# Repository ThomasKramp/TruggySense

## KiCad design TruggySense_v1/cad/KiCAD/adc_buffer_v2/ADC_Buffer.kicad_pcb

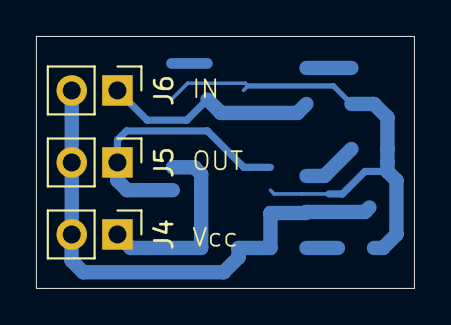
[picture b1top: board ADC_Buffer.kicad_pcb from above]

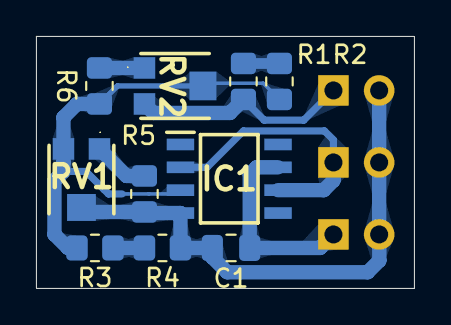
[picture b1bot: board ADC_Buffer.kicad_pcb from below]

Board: 2 copper layers, 21.0 x 14.0 mm, 13 parts (10 on the bottom side), 9 nets.

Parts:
C1: 10µ; C_0805_2012Metric_Pad1.18x1.45mm_HandSolder
IC1: OPA350UA_2K5; SOIC127P600X175-8N
J4, J5, J6: Conn_01x02; PinHeader_1x02_P2.54mm_Vertical
R1, R2, R3, R4, R5, R6: R; R_0805_2012Metric_Pad1.20x1.40mm_HandSolder
RV1, RV2: R; TC33X2503E

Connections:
GND: C1.2, IC1.4 (V-), J4.2, J5.2, J6.2, R4.1, R5.2, RV1.2
unnamed: IC1.3 (+IN), R2.2, R3.2, R6.2, RV1.3, RV2.2
unnamed: IC1.2 (-IN), IC1.6 (OUTPUT), J5.1
unnamed: J6.1, R1.1, RV2.3
unnamed: R1.2, R2.1
unnamed: R3.1, R4.2
unnamed: R5.1, RV1.1
unnamed: R6.1, RV2.1
VCC: C1.1, IC1.7 (V+), J4.1

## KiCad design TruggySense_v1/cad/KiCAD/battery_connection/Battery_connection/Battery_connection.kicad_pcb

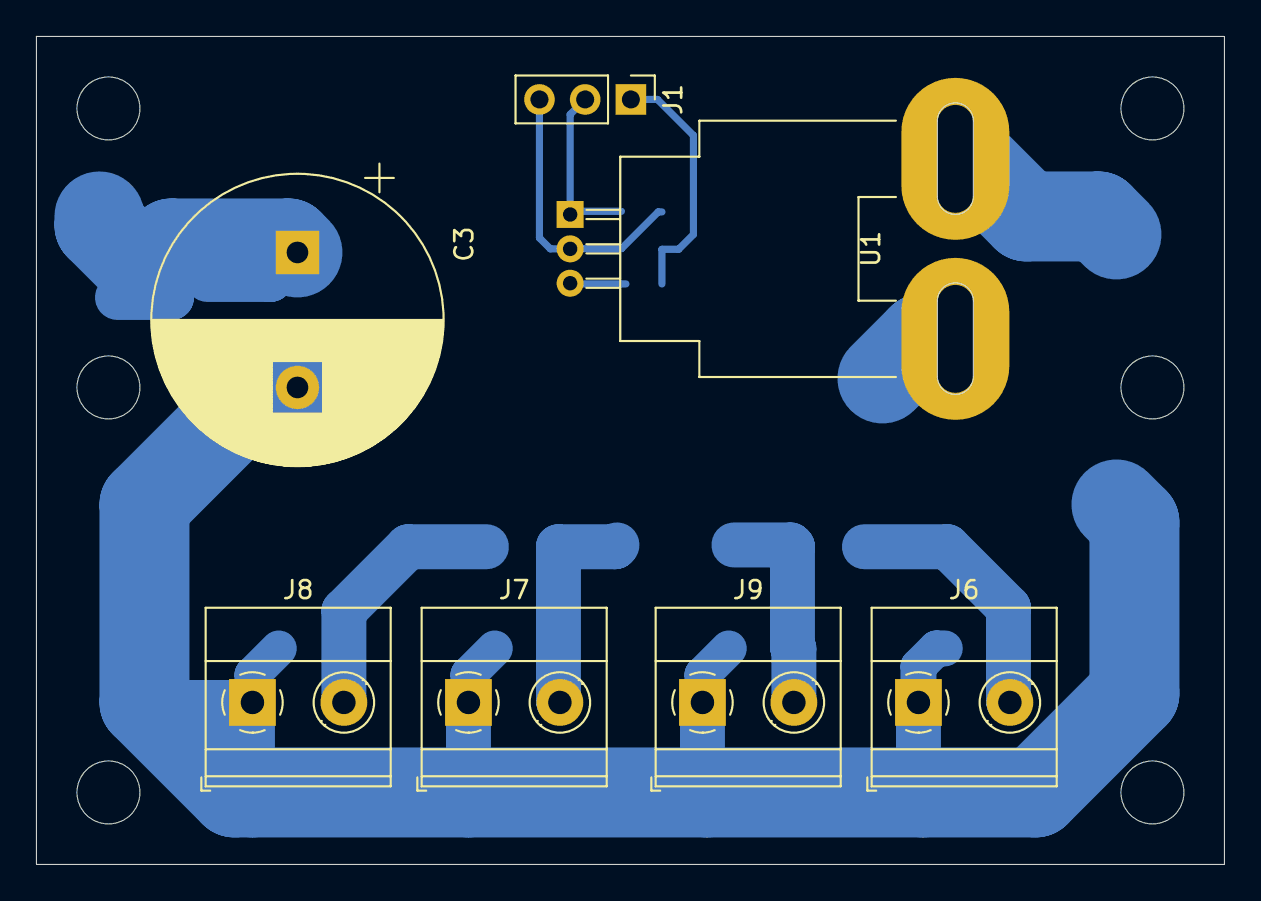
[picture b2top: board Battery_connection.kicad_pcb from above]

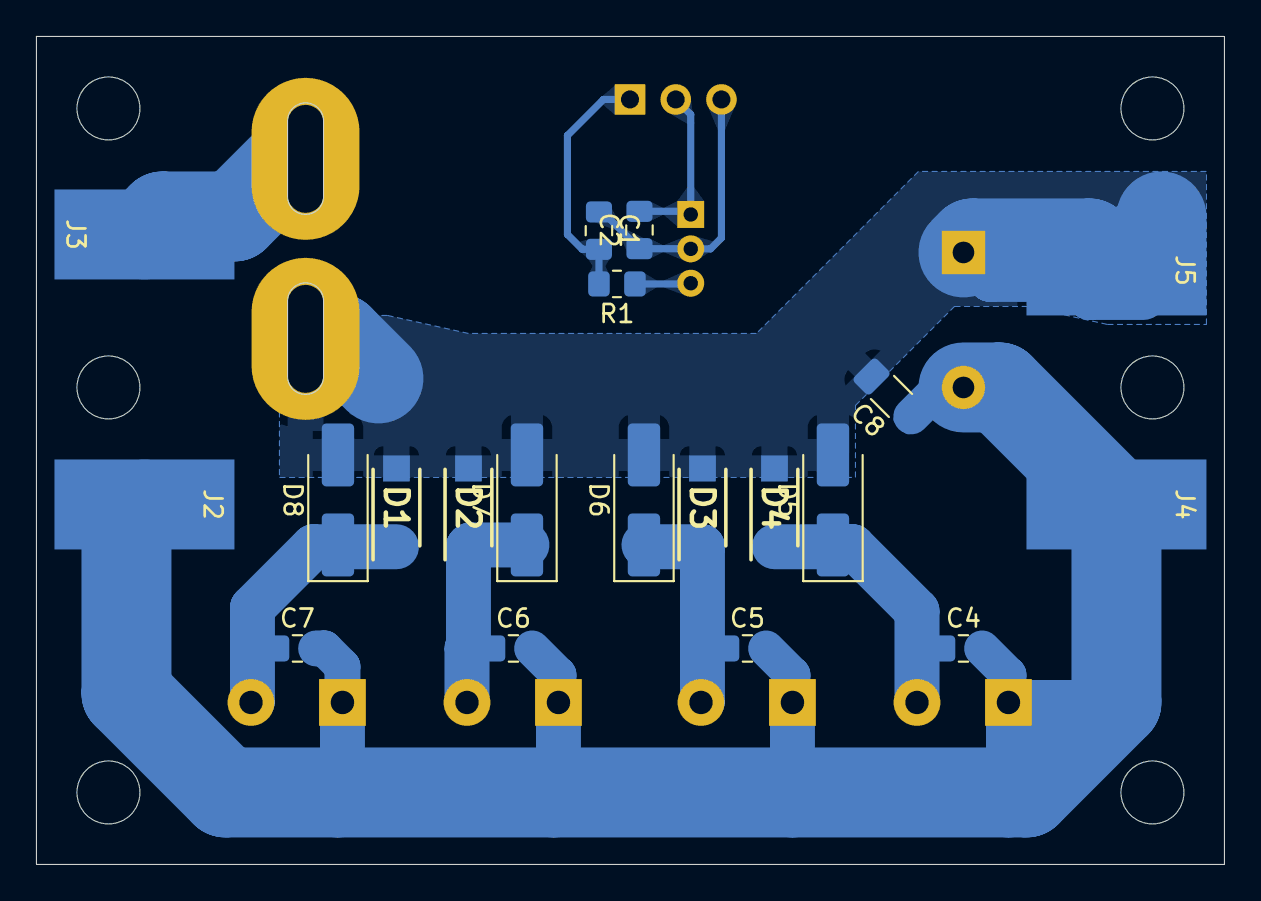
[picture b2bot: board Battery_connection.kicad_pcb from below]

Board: 2 copper layers, 66.0 x 46.0 mm, 27 parts (20 on the bottom side), 11 nets.

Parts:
C1: 1µ; C_0805_2012Metric_Pad1.18x1.45mm_HandSolder
C2: 100n; C_0805_2012Metric_Pad1.18x1.45mm_HandSolder
C3: 1000µ; CP_Radial_D16.0mm_P7.50mm
C4, C5, C6, C7: 10µ; C_0805_2012Metric_Pad1.18x1.45mm_HandSolder
C8: 10µ; C_1206_3216Metric_Pad1.33x1.80mm_HandSolder
D1, D2, D3, D4: VSSAF5M10HM3; SODFL5226X100N
D5, D6, D7, D8: 1N4007; D_SMA_Handsoldering
J1: Supply_I_Sens; PinHeader_1x03_P2.54mm_Vertical
J2: ESC-; SolderWirePad_1x01_SMD_5x10mm
J3: ESC+; SolderWirePad_1x01_SMD_5x10mm
J4: BAT-; SolderWirePad_1x01_SMD_5x10mm
J5: BAT+; SolderWirePad_1x01_SMD_5x10mm
J6: JET_5V; TerminalBlock_Phoenix_MKDS-1,5-2-5.08_1x02_P5.08mm_Horizont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
J7: TEENSY_3V3; TerminalBlock_Phoenix_MKDS-1,5-2-5.08_1x02_P5.08mm_Horizont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
J8: PHERI_3V3; TerminalBlock_Phoenix_MKDS-1,5-2-5.08_1x02_P5.08mm_Horizont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
J9: PHERI_5V; TerminalBlock_Phoenix_MKDS-1,5-2-5.08_1x02_P5.08mm_Horizont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
R1: 8k2; R_0805_2012Metric_Pad1.20x1.40mm_HandSolder
U1: ACS758xCB-200B-PFF; Allegro_CB_PFF

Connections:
+3.3V: C2.2, J1.2, U1.1 (VCC)
GND: C3.2, C4.2, C5.2, C6.2, C7.2, C8.1, J2.1, J4.1, J6.1, J7.1, J8.1, J9.1
GND2: C1.1, C2.1, J1.3, U1.2 (GND)
unnamed: C7.1, D1.1 (K), D8.1 (K), J6.2
unnamed: C6.1, D2.1 (K), D7.1 (K), J9.2
unnamed: C5.1, D3.1 (K), D6.1 (K), J7.2
unnamed: C4.1, D4.1 (K), D5.1 (K), J8.2
unnamed: C1.2, J1.1, R1.2
unnamed: J3.1, U1.5 (IP-)
unnamed: R1.1, U1.3 (VIOUT)
VCC: C3.1, C8.2, D1.2 (A), D2.2 (A), D3.2 (A), D4.2 (A), D5.2 (A), D6.2 (A), D7.2 (A), D8.2 (A), J5.1, U1.4 (IP+)

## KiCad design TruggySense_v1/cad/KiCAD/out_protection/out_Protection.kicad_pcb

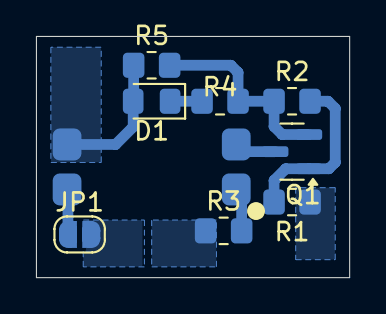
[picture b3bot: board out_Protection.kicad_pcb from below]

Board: 2 copper layers, 17.4 x 13.4 mm, 9 parts (9 on the bottom side), 7 nets.

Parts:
D1: LED; LED_0805_2012Metric_Pad1.15x1.40mm_HandSolder
JP1: SolderJumper_2_Open; SolderJumper-2_P1.3mm_Open_RoundedPad1.0x1.5mm
Q1: AO3400A; SOT-23
R1: 100; R_0805_2012Metric_Pad1.20x1.40mm_HandSolder
R2: 10k; R_0805_2012Metric_Pad1.20x1.40mm_HandSolder
R3: 39; R_0805_2012Metric_Pad1.20x1.40mm_HandSolder
R4: 330; R_0805_2012Metric_Pad1.20x1.40mm_HandSolder
R5: 1k; R_0805_2012Metric_Pad1.20x1.40mm_HandSolder
U1: VOS618A; VO617A

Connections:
/OUT_1: D1.2 (A), R5.1, U1.3
GND: Q1.2 (S), R2.1, R4.2, R5.2
unnamed: D1.1 (K), R4.1
unnamed: JP1.1 (A), U1.4
unnamed: Q1.3 (D), U1.2
unnamed: Q1.1 (G), R1.2, R2.2
unnamed: R3.2, U1.1

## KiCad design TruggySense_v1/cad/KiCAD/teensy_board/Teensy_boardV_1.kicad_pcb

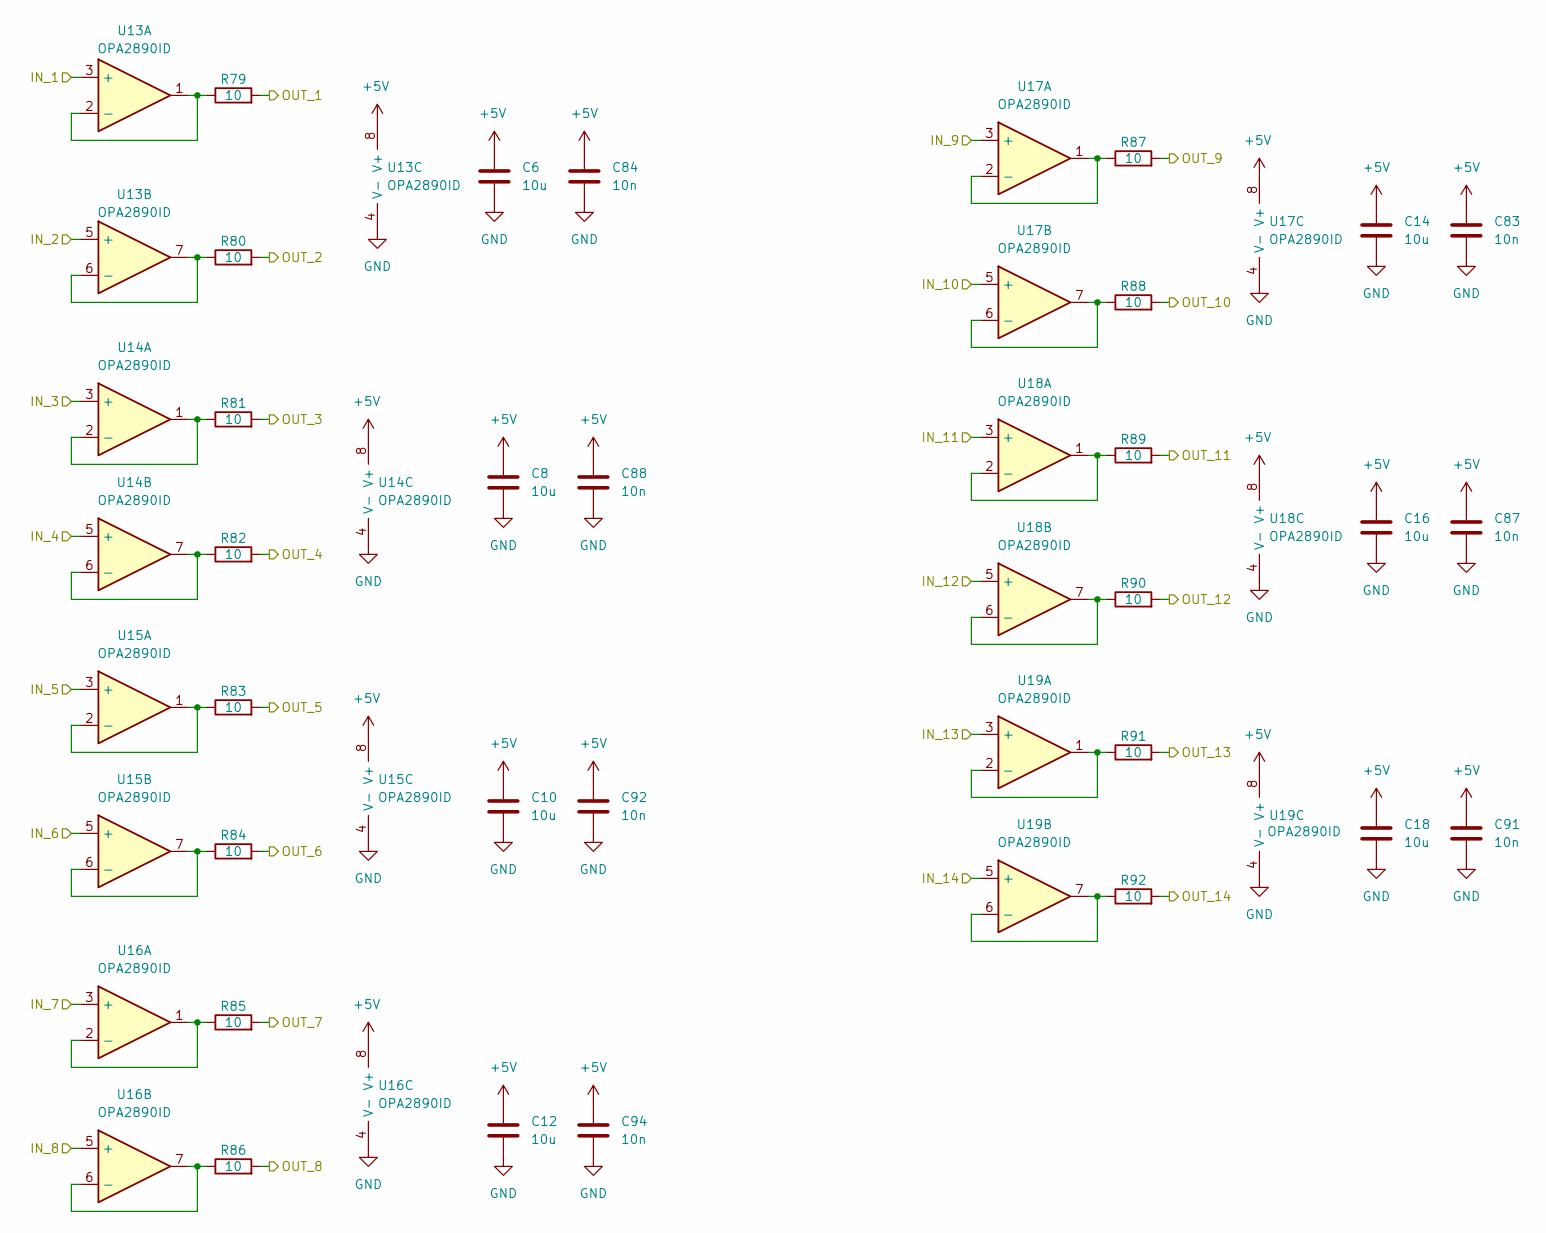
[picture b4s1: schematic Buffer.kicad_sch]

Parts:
C6, C8, C10, C12, C14, C16, C18: 10u; C_0805_2012Metric_Pad1.18x1.45mm_HandSolder
C83, C84, C87, C88, C91, C92, C94: 10n; C_0805_2012Metric_Pad1.18x1.45mm_HandSolder
R79, R80, R81, R82, R83, R84, R85, R86, R87, R88, R89, R90, R91, R92: 10; C_0805_2012Metric_Pad1.18x1.45mm_HandSolder
U13: OPA2890ID; SOIC-8_3.9x4.9mm_P1.27mm
U14, U15, U16, U17, U18, U19: OPA2890ID; SO-8_3.9x4.9mm_P1.27mm

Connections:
+5V: C6.1, C8.1, C10.1, C12.1, C14.1, C16.1, C18.1, C83.1, C84.1, C87.1, C88.1, C91.1, C92.1, C94.1, U13.8 (V+), U14.8 (V+), U15.8 (V+), U16.8 (V+), U17.8 (V+), U18.8 (V+), U19.8 (V+); also elsewhere on the board
/ADC inputs/Buffer/IN_1: U13.3 (+); also elsewhere on the board
/ADC inputs/Buffer/IN_2: U13.5 (+); also elsewhere on the board
/ADC inputs/Buffer/IN_3: U14.3 (+); also elsewhere on the board
/ADC inputs/Buffer/IN_4: U14.5 (+); also elsewhere on the board
/ADC inputs/Buffer/IN_5: U15.3 (+); also elsewhere on the board
/ADC inputs/Buffer/IN_6: U15.5 (+); also elsewhere on the board
/ADC inputs/Buffer/IN_7: U16.3 (+); also elsewhere on the board
/ADC inputs/Buffer/IN_8: U16.5 (+); also elsewhere on the board
/ADC inputs/Buffer/IN_9: U17.3 (+); also elsewhere on the board
/ADC inputs/Buffer/IN_10: U17.5 (+); also elsewhere on the board
/ADC inputs/Buffer/IN_11: U18.3 (+); also elsewhere on the board
/ADC inputs/Buffer/IN_12: U18.5 (+); also elsewhere on the board
/ADC inputs/Buffer/IN_13: U19.3 (+); also elsewhere on the board
/ADC inputs/Buffer/IN_14: U19.5 (+); also elsewhere on the board
/ADC inputs/Buffer/OUT_1: R79.2; also elsewhere on the board
/ADC inputs/Buffer/OUT_2: R80.2; also elsewhere on the board
/ADC inputs/Buffer/OUT_3: R81.2; also elsewhere on the board
/ADC inputs/Buffer/OUT_4: R82.2; also elsewhere on the board
/ADC inputs/Buffer/OUT_5: R83.2; also elsewhere on the board
/ADC inputs/Buffer/OUT_6: R84.2; also elsewhere on the board
/ADC inputs/Buffer/OUT_7: R85.2; also elsewhere on the board
/ADC inputs/Buffer/OUT_8: R86.2; also elsewhere on the board
/ADC inputs/Buffer/OUT_9: R87.2; also elsewhere on the board
/ADC inputs/Buffer/OUT_10: R88.2; also elsewhere on the board
/ADC inputs/Buffer/OUT_11: R89.2; also elsewhere on the board
/ADC inputs/Buffer/OUT_12: R90.2; also elsewhere on the board
/ADC inputs/Buffer/OUT_13: R91.2; also elsewhere on the board
/ADC inputs/Buffer/OUT_14: R92.2; also elsewhere on the board
GND: C6.2, C8.2, C10.2, C12.2, C14.2, C16.2, C18.2, C83.2, C84.2, C87.2, C88.2, C91.2, C92.2, C94.2, U13.4 (V-), U14.4 (V-), U15.4 (V-), U16.4 (V-), U17.4 (V-), U18.4 (V-), U19.4 (V-); also elsewhere on the board
unnamed: R79.1, U13.1, U13.2 (-)
unnamed: R80.1, U13.6 (-), U13.7
unnamed: R81.1, U14.1, U14.2 (-)
unnamed: R82.1, U14.6 (-), U14.7
unnamed: R83.1, U15.1, U15.2 (-)
unnamed: R84.1, U15.6 (-), U15.7
unnamed: R85.1, U16.1, U16.2 (-)
unnamed: R86.1, U16.6 (-), U16.7
unnamed: R87.1, U17.1, U17.2 (-)
unnamed: R88.1, U17.6 (-), U17.7
unnamed: R89.1, U18.1, U18.2 (-)
unnamed: R90.1, U18.6 (-), U18.7
unnamed: R91.1, U19.1, U19.2 (-)
unnamed: R92.1, U19.6 (-), U19.7

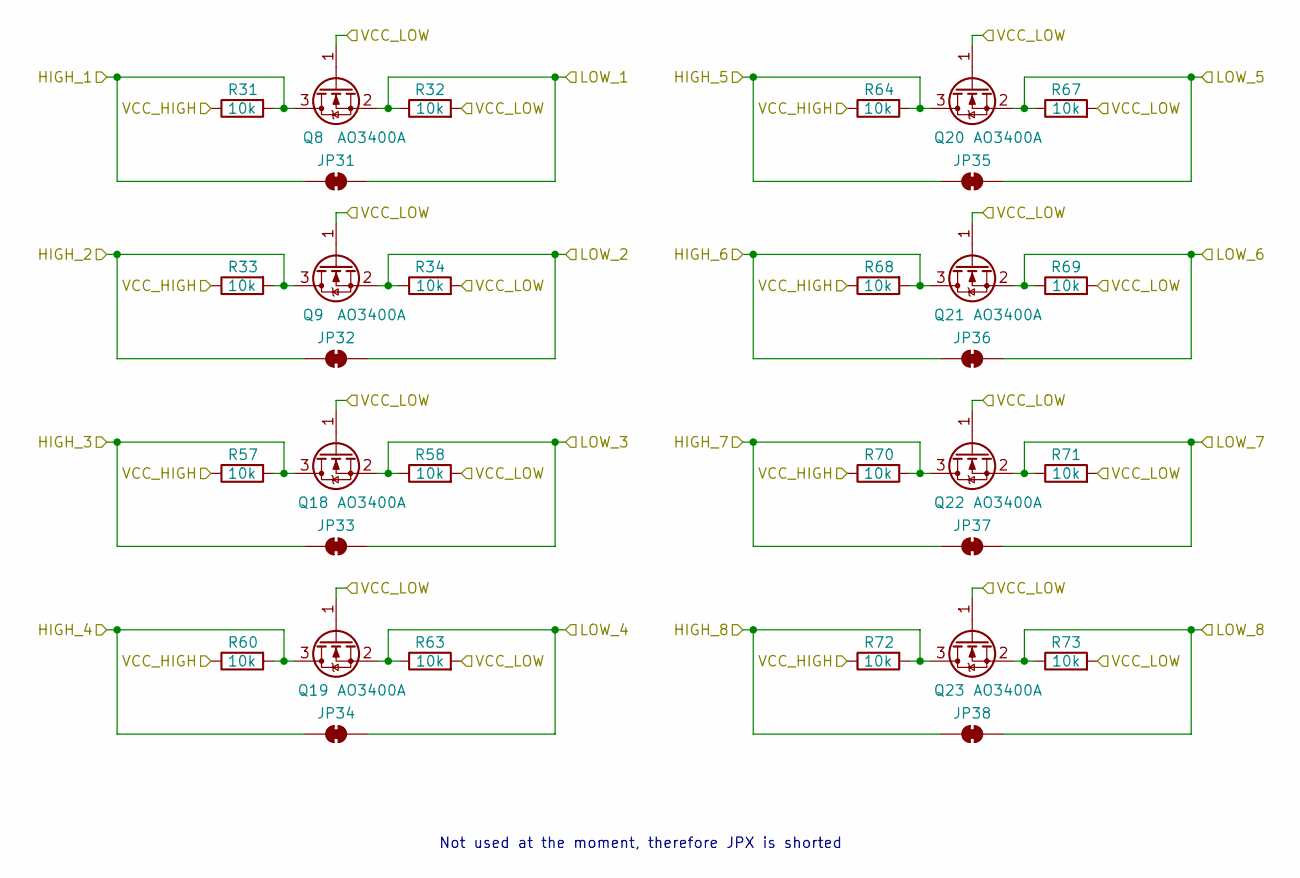
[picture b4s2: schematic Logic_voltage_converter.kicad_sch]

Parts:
JP31, JP32, JP33, JP34, JP35, JP36, JP37, JP38: SolderJumper_2_Bridged; SolderJumper-2_P1.3mm_Bridged_RoundedPad1.0x1.5mm
Q8, Q9, Q18, Q19, Q20, Q21, Q22, Q23: AO3400A; SOT-23
R31, R32, R33, R34, R57, R58, R60, R63, R64, R67, R68, R69, R70, R71, R72, R73: 10k; R_0805_2012Metric_Pad1.20x1.40mm_HandSolder

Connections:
+5V: R31.1, R33.1, R57.1, R60.1, R64.1, R68.1, R70.1, R72.1; also elsewhere on the board
/Communication & pheripherals/Logic_voltage_converter/HIGH_1: JP31.1 (A), Q8.3 (D), R31.2; also elsewhere on the board
/Communication & pheripherals/Logic_voltage_converter/HIGH_2: JP32.1 (A), Q9.3 (D), R33.2; also elsewhere on the board
/Communication & pheripherals/Logic_voltage_converter/HIGH_3: JP33.1 (A), Q18.3 (D), R57.2; also elsewhere on the board
/Communication & pheripherals/Logic_voltage_converter/HIGH_4: JP34.1 (A), Q19.3 (D), R60.2; also elsewhere on the board
/Communication & pheripherals/Logic_voltage_converter/HIGH_5: JP35.1 (A), Q20.3 (D), R64.2; also elsewhere on the board
/Communication & pheripherals/Logic_voltage_converter/HIGH_6: JP36.1 (A), Q21.3 (D), R68.2; also elsewhere on the board
/Communication & pheripherals/Logic_voltage_converter/HIGH_7: JP37.1 (A), Q22.3 (D), R70.2; also elsewhere on the board
/Communication & pheripherals/Logic_voltage_converter/HIGH_8: JP38.1 (A), Q23.3 (D), R72.2; also elsewhere on the board
/Communication & pheripherals/Logic_voltage_converter/LOW_1: JP31.2 (B), Q8.2 (S), R32.1; also elsewhere on the board
/Communication & pheripherals/Logic_voltage_converter/LOW_2: JP32.2 (B), Q9.2 (S), R34.1; also elsewhere on the board
/Communication & pheripherals/Logic_voltage_converter/LOW_3: JP33.2 (B), Q18.2 (S), R58.1; also elsewhere on the board
/Communication & pheripherals/Logic_voltage_converter/LOW_4: JP34.2 (B), Q19.2 (S), R63.1; also elsewhere on the board
/Communication & pheripherals/Logic_voltage_converter/LOW_5: JP35.2 (B), Q20.2 (S), R67.1; also elsewhere on the board
/Communication & pheripherals/Logic_voltage_converter/LOW_6: JP36.2 (B), Q21.2 (S), R69.1; also elsewhere on the board
/Communication & pheripherals/Logic_voltage_converter/LOW_7: JP37.2 (B), Q22.2 (S), R71.1; also elsewhere on the board
/Communication & pheripherals/Logic_voltage_converter/LOW_8: JP38.2 (B), Q23.2 (S), R73.1; also elsewhere on the board

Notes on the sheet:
Not used at the moment, therefore JPX is shorted

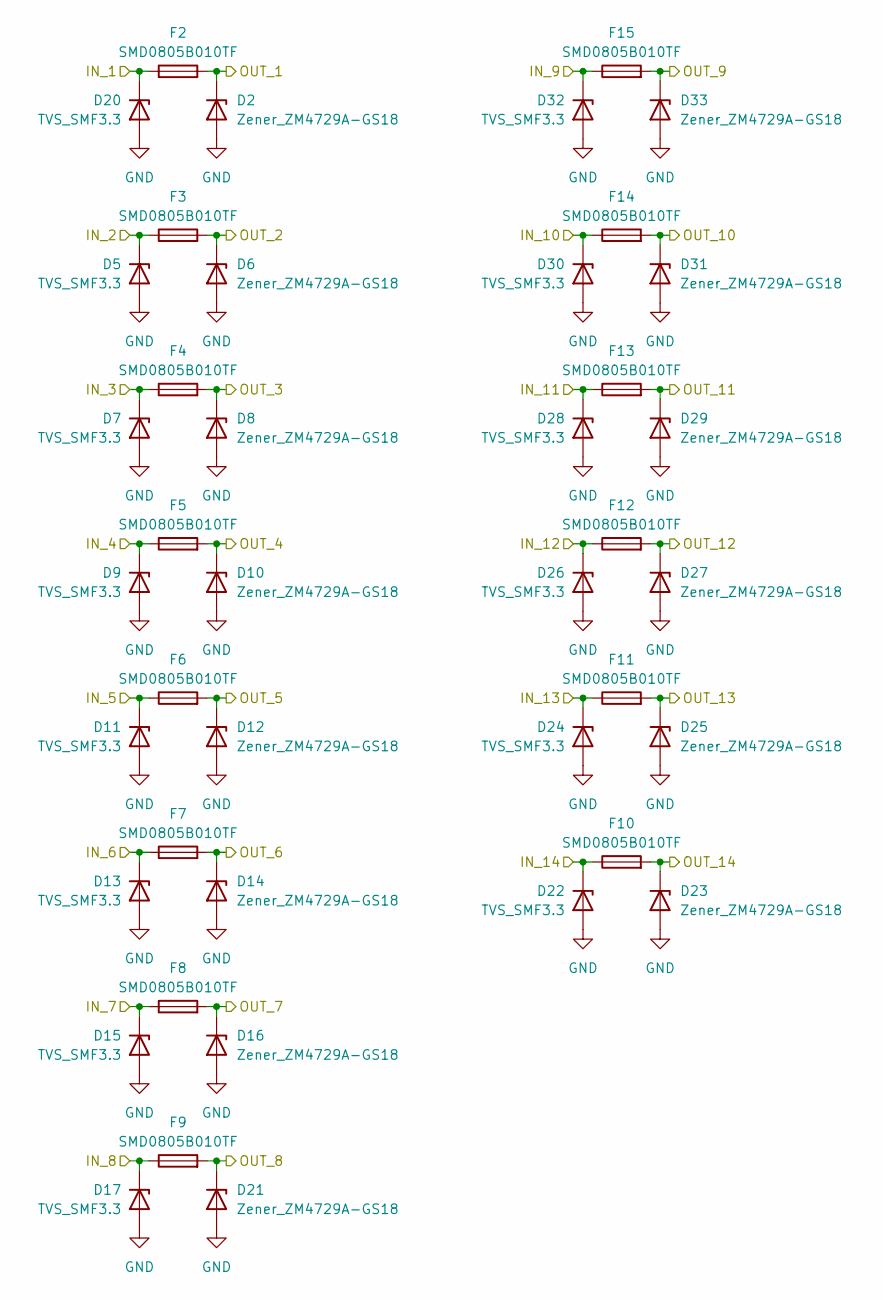
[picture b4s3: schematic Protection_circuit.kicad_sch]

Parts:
D2, D6, D8, D10, D12, D14, D16, D21, D23, D25, D27, D29, D31, D33: Zener_ZM4729A-GS18; D_MELF
D5, D7, D9, D11, D13, D15, D17, D20, D22, D24, D26, D28, D30, D32: TVS_SMF3.3; SOD3718X108N
F2, F3, F4, F5, F6, F7, F8, F9, F10, F11, F12, F13, F14, F15: SMD0805B010TF; Fuse_0805_2012Metric_Pad1.15x1.40mm_HandSolder

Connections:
/ADC inputs/Protection_circuit_ADC1/IN_1: D20.1 (K), F2.1; also elsewhere on the board
/ADC inputs/Protection_circuit_ADC1/IN_2: D5.1 (K), F3.1; also elsewhere on the board
/ADC inputs/Protection_circuit_ADC1/IN_3: D7.1 (K), F4.1; also elsewhere on the board
/ADC inputs/Protection_circuit_ADC1/IN_4: D9.1 (K), F5.1; also elsewhere on the board
/ADC inputs/Protection_circuit_ADC1/IN_5: D11.1 (K), F6.1; also elsewhere on the board
/ADC inputs/Protection_circuit_ADC1/IN_6: D13.1 (K), F7.1; also elsewhere on the board
/ADC inputs/Protection_circuit_ADC1/IN_7: D15.1 (K), F8.1; also elsewhere on the board
/ADC inputs/Protection_circuit_ADC1/IN_8: D17.1 (K), F9.1; also elsewhere on the board
/ADC inputs/Protection_circuit_ADC1/IN_9: D32.1 (K), F15.1; also elsewhere on the board
/ADC inputs/Protection_circuit_ADC1/IN_10: D30.1 (K), F14.1; also elsewhere on the board
/ADC inputs/Protection_circuit_ADC1/IN_11: D28.1 (K), F13.1; also elsewhere on the board
/ADC inputs/Protection_circuit_ADC1/IN_12: D26.1 (K), F12.1; also elsewhere on the board
/ADC inputs/Protection_circuit_ADC1/IN_13: D24.1 (K), F11.1; also elsewhere on the board
/ADC inputs/Protection_circuit_ADC1/IN_14: D22.1 (K), F10.1; also elsewhere on the board
/ADC inputs/Protection_circuit_ADC1/OUT_1: D2.1 (K), F2.2; also elsewhere on the board
/ADC inputs/Protection_circuit_ADC1/OUT_2: D6.1 (K), F3.2; also elsewhere on the board
/ADC inputs/Protection_circuit_ADC1/OUT_3: D8.1 (K), F4.2; also elsewhere on the board
/ADC inputs/Protection_circuit_ADC1/OUT_4: D10.1 (K), F5.2; also elsewhere on the board
/ADC inputs/Protection_circuit_ADC1/OUT_5: D12.1 (K), F6.2; also elsewhere on the board
/ADC inputs/Protection_circuit_ADC1/OUT_6: D14.1 (K), F7.2; also elsewhere on the board
/ADC inputs/Protection_circuit_ADC1/OUT_7: D16.1 (K), F8.2; also elsewhere on the board
/ADC inputs/Protection_circuit_ADC1/OUT_8: D21.1 (K), F9.2; also elsewhere on the board
/ADC inputs/Protection_circuit_ADC1/OUT_9: D33.1 (K), F15.2; also elsewhere on the board
/ADC inputs/Protection_circuit_ADC1/OUT_10: D31.1 (K), F14.2; also elsewhere on the board
/ADC inputs/Protection_circuit_ADC1/OUT_11: D29.1 (K), F13.2; also elsewhere on the board
/ADC inputs/Protection_circuit_ADC1/OUT_12: D27.1 (K), F12.2; also elsewhere on the board
/ADC inputs/Protection_circuit_ADC1/OUT_13: D25.1 (K), F11.2; also elsewhere on the board
/ADC inputs/Protection_circuit_ADC1/OUT_14: D23.1 (K), F10.2; also elsewhere on the board
GND: D2.2 (A), D5.2 (A), D6.2 (A), D7.2 (A), D8.2 (A), D9.2 (A), D10.2 (A), D11.2 (A), D12.2 (A), D13.2 (A), D14.2 (A), D15.2 (A), D16.2 (A), D17.2 (A), D20.2 (A), D21.2 (A), D22.2 (A), D23.2 (A), D24.2 (A), D25.2 (A), D26.2 (A), D27.2 (A), D28.2 (A), D29.2 (A), D30.2 (A), D31.2 (A), D32.2 (A), D33.2 (A); also elsewhere on the board

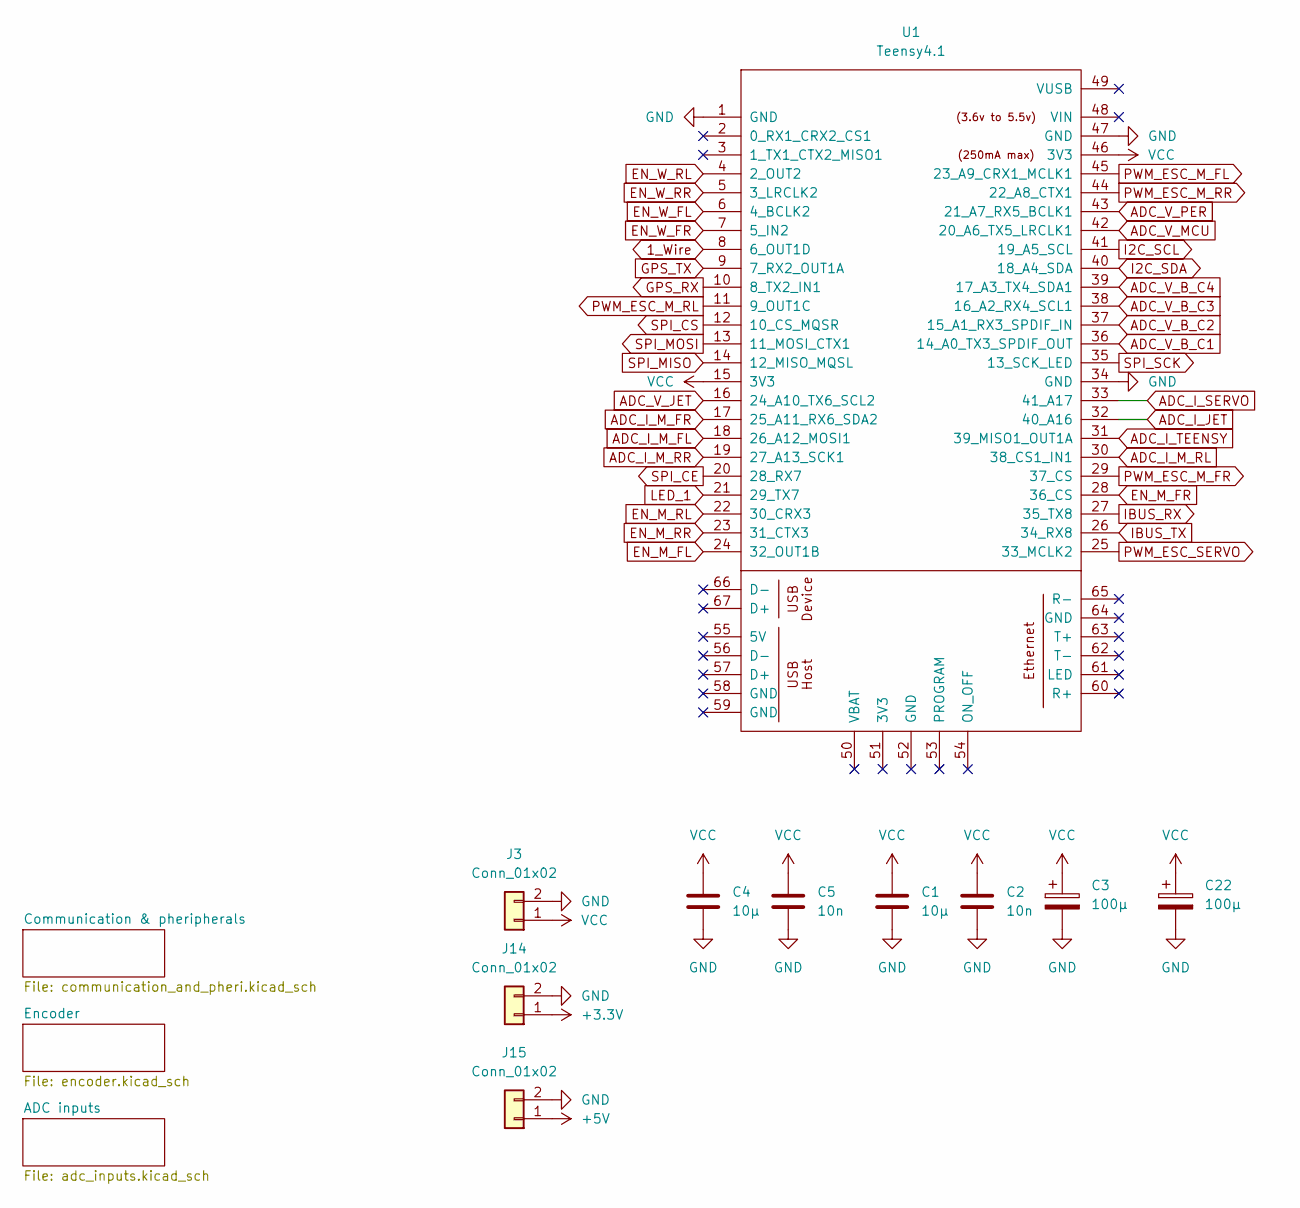
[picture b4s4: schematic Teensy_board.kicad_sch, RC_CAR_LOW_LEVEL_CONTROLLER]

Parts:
C1, C4: 10µ; C_0805_2012Metric_Pad1.18x1.45mm_HandSolder
C2, C5: 10n; C_0805_2012Metric_Pad1.18x1.45mm_HandSolder
C3, C22: 100µ; CP_Radial_D5.0mm_P2.00mm
J3, J14, J15: Conn_01x02; PinSocket_1x02_P2.54mm_Vertical
U1: Teensy4.1; Teensy41

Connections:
1_Wire: U1.8 (6_OUT1D); also elsewhere on the board
+5V: J15.1; also elsewhere on the board
ADC_I_JET: U1.32 (40_A16); also elsewhere on the board
ADC_I_M_FL: U1.18 (26_A12_MOSI1); also elsewhere on the board
ADC_I_M_FR: U1.17 (25_A11_RX6_SDA2); also elsewhere on the board
ADC_I_M_RL: U1.30 (38_CS1_IN1); also elsewhere on the board
ADC_I_M_RR: U1.19 (27_A13_SCK1); also elsewhere on the board
ADC_I_SERVO: U1.33 (41_A17); also elsewhere on the board
ADC_I_TEENSY: U1.31 (39_MISO1_OUT1A); also elsewhere on the board
ADC_V_B_C1: U1.36 (14_A0_TX3_SPDIF_OUT); also elsewhere on the board
ADC_V_B_C2: U1.37 (15_A1_RX3_SPDIF_IN); also elsewhere on the board
ADC_V_B_C3: U1.38 (16_A2_RX4_SCL1); also elsewhere on the board
ADC_V_B_C4: U1.39 (17_A3_TX4_SDA1); also elsewhere on the board
ADC_V_JET: U1.16 (24_A10_TX6_SCL2); also elsewhere on the board
ADC_V_MCU: U1.42 (20_A6_TX5_LRCLK1); also elsewhere on the board
ADC_V_PER: U1.43 (21_A7_RX5_BCLK1); also elsewhere on the board
EN_M_FL: U1.24 (32_OUT1B); also elsewhere on the board
EN_M_FR: U1.28 (36_CS); also elsewhere on the board
EN_M_RL: U1.22 (30_CRX3); also elsewhere on the board
EN_M_RR: U1.23 (31_CTX3); also elsewhere on the board
EN_W_FL: U1.6 (4_BCLK2); also elsewhere on the board
EN_W_FR: U1.7 (5_IN2); also elsewhere on the board
EN_W_RL: U1.4 (2_OUT2); also elsewhere on the board
EN_W_RR: U1.5 (3_LRCLK2); also elsewhere on the board
GND: C1.2, C2.2, C3.2, C4.2, C5.2, C22.2, J3.2, J14.2, J15.2, U1.1 (GND), U1.34 (GND), U1.47 (GND); also elsewhere on the board
GPS_RX: U1.10 (8_TX2_IN1); also elsewhere on the board
GPS_TX: U1.9 (7_RX2_OUT1A); also elsewhere on the board
I2C_SCL: U1.41 (19_A5_SCL); also elsewhere on the board
I2C_SDA: U1.40 (18_A4_SDA); also elsewhere on the board
IBUS_RX: U1.27 (35_TX8); also elsewhere on the board
IBUS_TX: U1.26 (34_RX8); also elsewhere on the board
PWM_ESC_M_FL: U1.45 (23_A9_CRX1_MCLK1); also elsewhere on the board
PWM_ESC_M_FR: U1.29 (37_CS); also elsewhere on the board
PWM_ESC_M_RL: U1.11 (9_OUT1C); also elsewhere on the board
PWM_ESC_M_RR: U1.44 (22_A8_CTX1); also elsewhere on the board
PWM_ESC_SERVO: U1.25 (33_MCLK2); also elsewhere on the board
SPI_CS: U1.12 (10_CS_MQSR); also elsewhere on the board
SPI_MISO: U1.14 (12_MISO_MQSL); also elsewhere on the board
SPI_MOSI: U1.13 (11_MOSI_CTX1); also elsewhere on the board
SPI_SCK: U1.35 (13_SCK_LED); also elsewhere on the board
VCC: C1.1, C2.1, C3.1, C4.1, C5.1, C22.1, J3.1, U1.15 (3V3), U1.46 (3V3)
